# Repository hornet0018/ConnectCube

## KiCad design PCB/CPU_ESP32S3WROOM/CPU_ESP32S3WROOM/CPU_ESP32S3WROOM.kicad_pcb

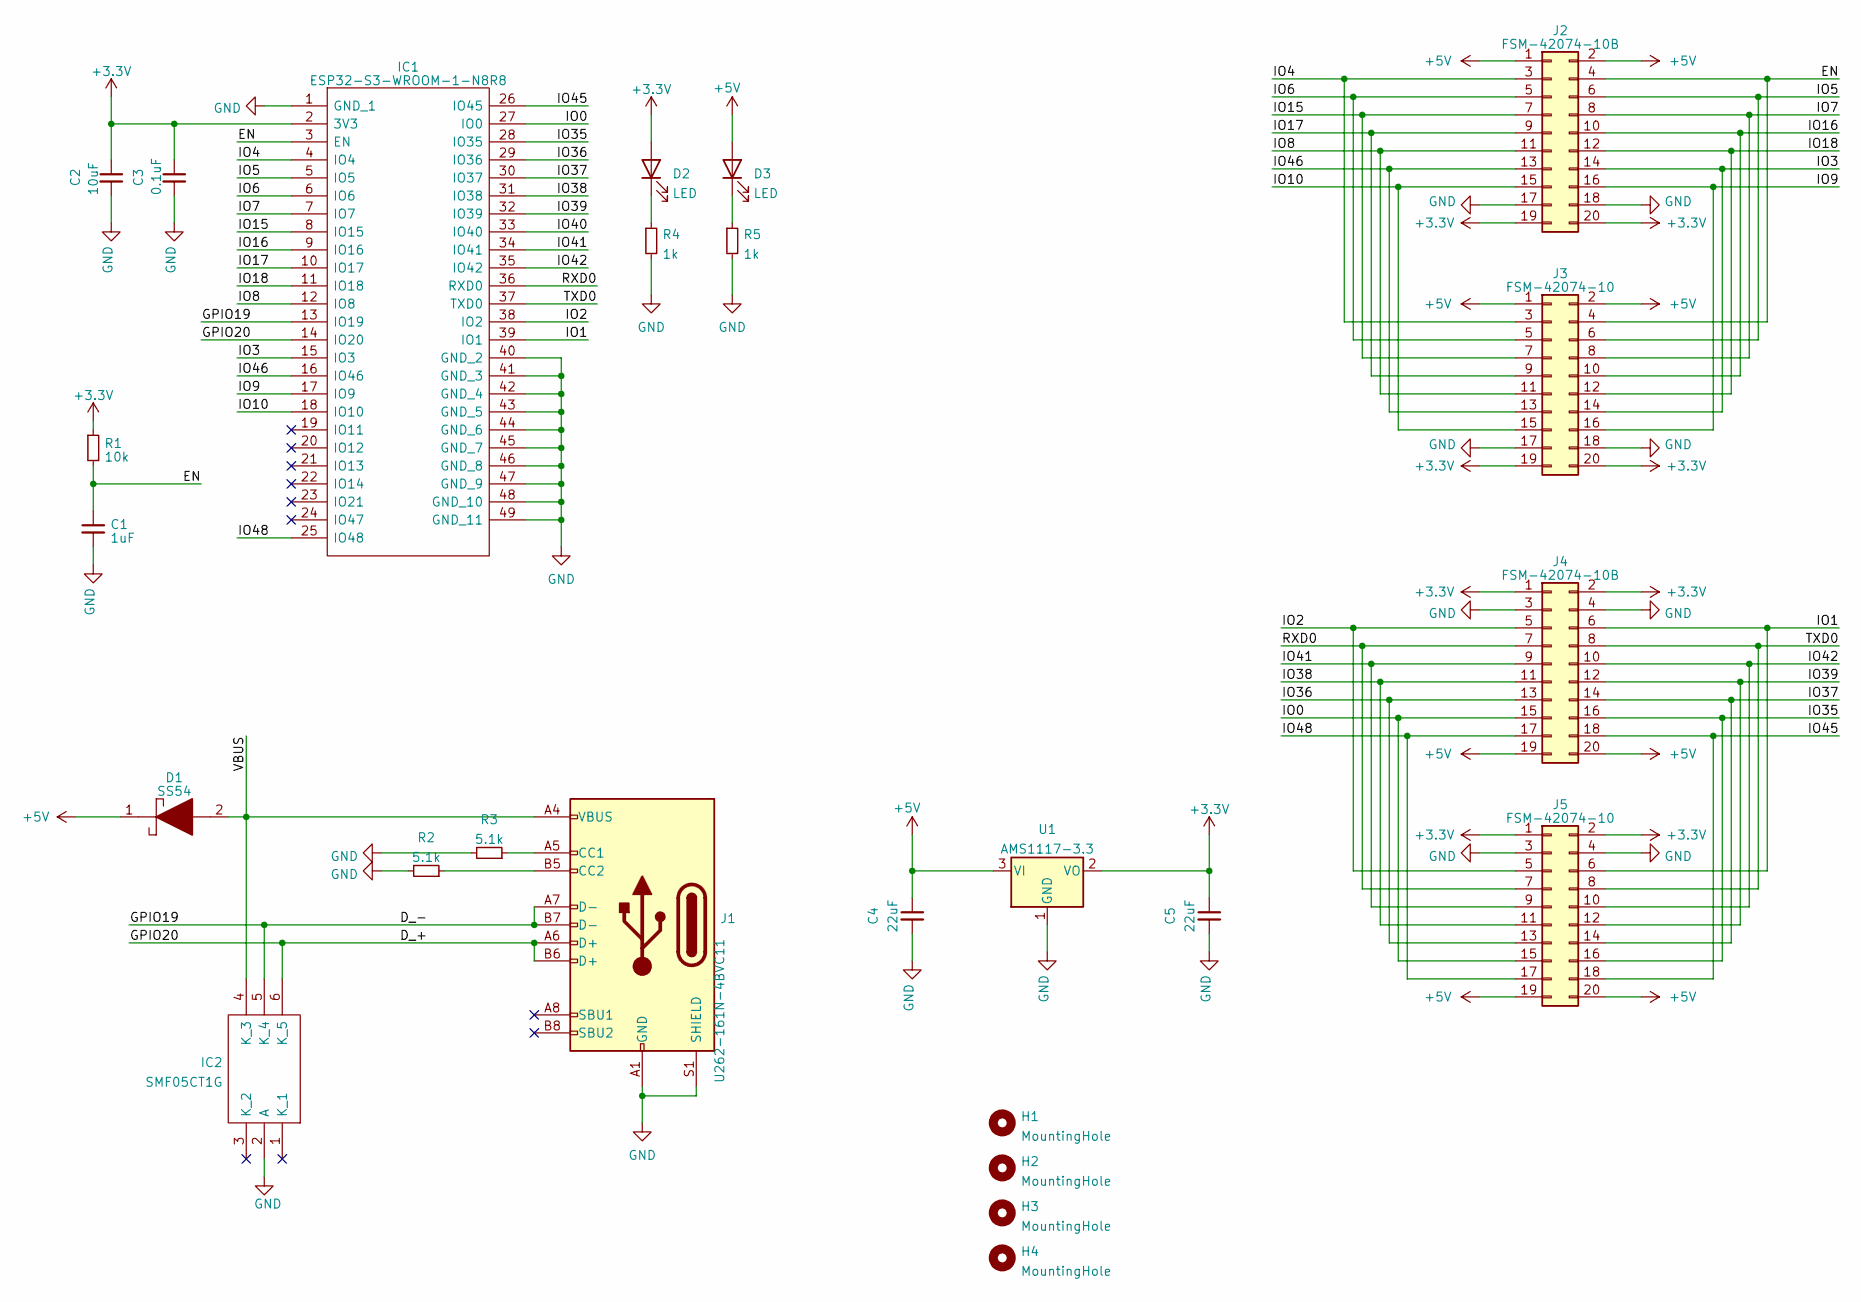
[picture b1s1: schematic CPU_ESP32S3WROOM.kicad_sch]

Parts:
C1: 1uF; C_0603_1608Metric_Pad1.08x0.95mm_HandSolder
C2: 10uF; C_0603_1608Metric_Pad1.08x0.95mm_HandSolder
C3: 0.1uF; C_0603_1608Metric_Pad1.08x0.95mm_HandSolder
C4, C5: 22uF; C_0603_1608Metric_Pad1.08x0.95mm_HandSolder
D1: SS54; DIOM5026X262N; Manufacturer_Part_Number SS54
D2, D3: LED; LED_0603_1608Metric_Pad1.05x0.95mm_HandSolder
H1, H2, H3, H4: MountingHole; MountingHole_3.2mm_M3_Pad_Via
IC1: ESP32-S3-WROOM-1-N8R8; ESP32S3WROOM1N8R8; Manufacturer_Part_Number ESP32-S3-WROOM-1-N8R8; Mouser Part Number 356-EP32S3WROOM1N8R8
IC2: SMF05CT1G; SOT65P210X110-6N; Manufacturer_Part_Number SMF05CT1G; Mouser Part Number 863-SMF05CT1G
J1: U262-161N-4BVC11; U262-16XN-4BVC11
J2, J4: FSM-42074-10B; PinSocket_2x10_P2.54mm_Vertical_SMD
J3, J5: FSM-42074-10; PinHeader_2x10_P2.54mm_Vertical_SMD
R1: 10k; R_0603_1608Metric_Pad0.98x0.95mm_HandSolder
R2, R3: 5.1k; R_0603_1608Metric_Pad0.98x0.95mm_HandSolder
R4, R5: 1k; R_0603_1608Metric_Pad0.98x0.95mm_HandSolder
U1: AMS1117-3.3; SOT-223-3_TabPin2

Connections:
+3V3: C2.1, C3.1, C5.1, D2.2 (A), IC1.2 (3V3), J2.19, J2.20, J3.19, J3.20, J4.1, J4.2, J5.1, J5.2, R1.1, U1.2 (VO)
+5V: C4.1, D1.1, D3.2 (A), J2.1, J2.2, J3.1, J3.2, J4.19, J4.20, J5.19, J5.20, U1.3 (VI)
/D_+: IC1.14 (IO20), IC2.6 (K_5), J1.A6 (D+), J1.B6 (D+)
/D_-: IC1.13 (IO19), IC2.5 (K_4), J1.A7 (D-), J1.B7 (D-)
/EN: C1.1, IC1.3 (EN), J2.4, J3.4, R1.2
/IO0: IC1.27 (IO0), J4.15, J5.15
/IO1: IC1.39 (IO1), J4.6, J5.6
/IO2: IC1.38 (IO2), J4.5, J5.5
/IO3: IC1.15 (IO3), J2.14, J3.14
/IO4: IC1.4 (IO4), J2.3, J3.3
/IO5: IC1.5 (IO5), J2.6, J3.6
/IO6: IC1.6 (IO6), J2.5, J3.5
/IO7: IC1.7 (IO7), J2.8, J3.8
/IO8: IC1.12 (IO8), J2.11, J3.11
/IO9: IC1.17 (IO9), J2.16, J3.16
/IO10: IC1.18 (IO10), J2.15, J3.15
/IO15: IC1.8 (IO15), J2.7, J3.7
/IO16: IC1.9 (IO16), J2.10, J3.10
/IO17: IC1.10 (IO17), J2.9, J3.9
/IO18: IC1.11 (IO18), J2.12, J3.12
/IO35: IC1.28 (IO35), J4.16, J5.16
/IO36: IC1.29 (IO36), J4.13, J5.13
/IO37: IC1.30 (IO37), J4.14, J5.14
/IO38: IC1.31 (IO38), J4.11, J5.11
/IO39: IC1.32 (IO39), J4.12, J5.12
/IO40: IC1.33 (IO40)
/IO41: IC1.34 (IO41), J4.9, J5.9
/IO42: IC1.35 (IO42), J4.10, J5.10
/IO45: IC1.26 (IO45), J4.18, J5.18
/IO46: IC1.16 (IO46), J2.13, J3.13
/IO48: IC1.25 (IO48), J4.17, J5.17
/RXD0: IC1.36 (RXD0), J4.7, J5.7
/TXD0: IC1.37 (TXD0), J4.8, J5.8
/VBUS: D1.2, IC2.4 (K_3), J1.A4 (VBUS), J1.A9 (VBUS), J1.B4 (VBUS), J1.B9 (VBUS)
GND: C1.2, C2.2, C3.2, C4.2, C5.2, IC1.1 (GND_1), IC1.40 (GND_2), IC1.41 (GND_3), IC1.42 (GND_4), IC1.43 (GND_5), IC1.44 (GND_6), IC1.45 (GND_7), IC1.46 (GND_8), IC1.47 (GND_9), IC1.48 (GND_10), IC1.49 (GND_11), IC2.2 (A), J1.A1 (GND), J1.A12 (GND), J1.B1 (GND), J1.B12 (GND), J1.S1 (SHIELD), J2.17, J2.18, J3.17, J3.18, J4.3, J4.4, J5.3, J5.4, R2.2, R3.2, R4.2, R5.2, U1.1 (GND)
unnamed: D2.1 (K), R4.1
unnamed: D3.1 (K), R5.1
unnamed: J1.A5 (CC1), R3.1
unnamed: J1.B5 (CC2), R2.1

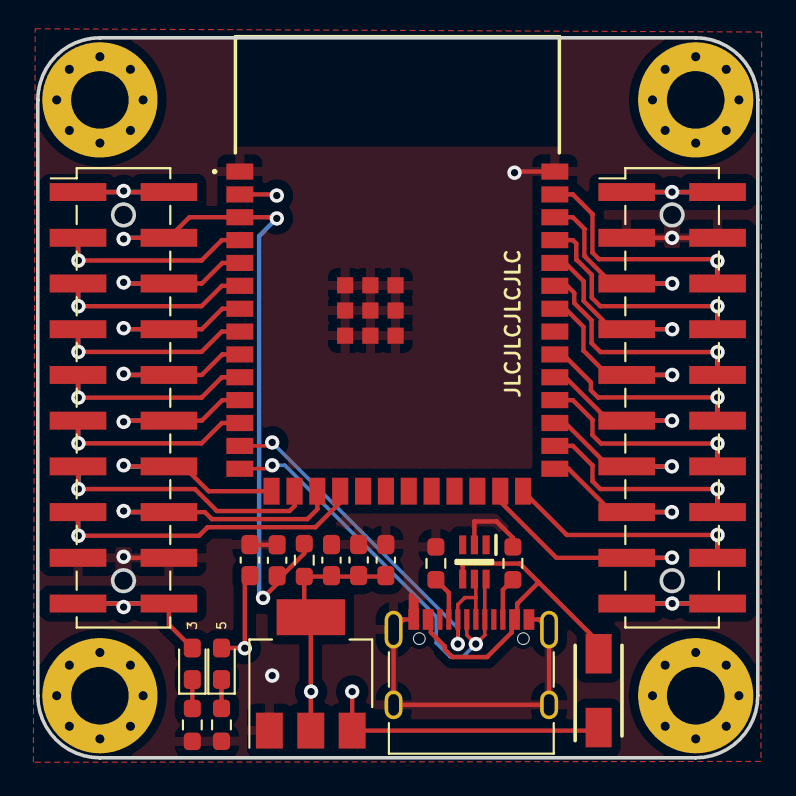
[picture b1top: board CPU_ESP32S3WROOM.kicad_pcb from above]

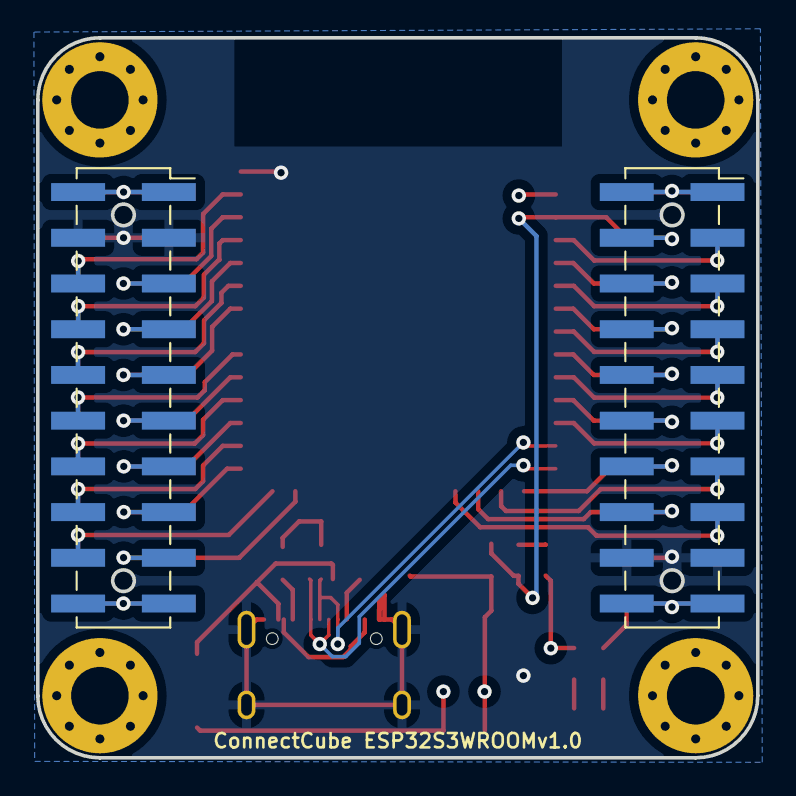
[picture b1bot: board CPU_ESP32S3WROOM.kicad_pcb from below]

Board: 6 copper layers, 40.0 x 40.0 mm, 25 parts (2 on the bottom side), 38 nets.

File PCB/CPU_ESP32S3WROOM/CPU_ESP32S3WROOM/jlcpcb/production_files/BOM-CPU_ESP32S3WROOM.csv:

Comment,Designator,Footprint,LCSC
0.1uF,C3,C_0603_1608Metric_Pad1.08x0.95mm_HandSolder,C14858
1uF,C1,C_0603_1608Metric_Pad1.08x0.95mm_HandSolder,C15849
SMF05CT1G,IC2,SOT65P210X110-6N,C15879
10uF,C2,C_0603_1608Metric_Pad1.08x0.95mm_HandSolder,C19702
1k,"R4,R5",R_0603_1608Metric_Pad0.98x0.95mm_HandSolder,C21190
SS54,D1,DIOM5026X262N,C22452
5.1k,"R2,R3",R_0603_1608Metric_Pad0.98x0.95mm_HandSolder,C23186
10k,R1,R_0603_1608Metric_Pad0.98x0.95mm_HandSolder,C25804
U262-161N-4BVC11,J1,U262-16XN-4BVC11,C319148
22uF,"C4,C5",C_0603_1608Metric_Pad1.08x0.95mm_HandSolder,C59461
AMS1117-3.3,U1,SOT-223-3_TabPin2,C6186
LED,D3,LED_0603_1608Metric_Pad1.05x0.95mm_HandSolder,C72041
LED,D2,LED_0603_1608Metric_Pad1.05x0.95mm_HandSolder,C72043
FSM-42074-10,J5,PinHeader_2x10_P2.54mm_Vertical_SMD,
MountingHole,H2,MountingHole_3.2mm_M3_Pad_Via,
MountingHole,H4,MountingHole_3.2mm_M3_Pad_Via,
MountingHole,H3,MountingHole_3.2mm_M3_Pad_Via,
MountingHole,H1,MountingHole_3.2mm_M3_Pad_Via,
FSM-42074-10,J3,PinHeader_2x10_P2.54mm_Vertical_SMD,
ESP32-S3-WROOM-1-N8R8,IC1,ESP32S3WROOM1N8R8,
FSM-42074-10B,J4,PinSocket_2x10_P2.54mm_Vertical_SMD,
FSM-42074-10B,J2,PinSocket_2x10_P2.54mm_Vertical_SMD,

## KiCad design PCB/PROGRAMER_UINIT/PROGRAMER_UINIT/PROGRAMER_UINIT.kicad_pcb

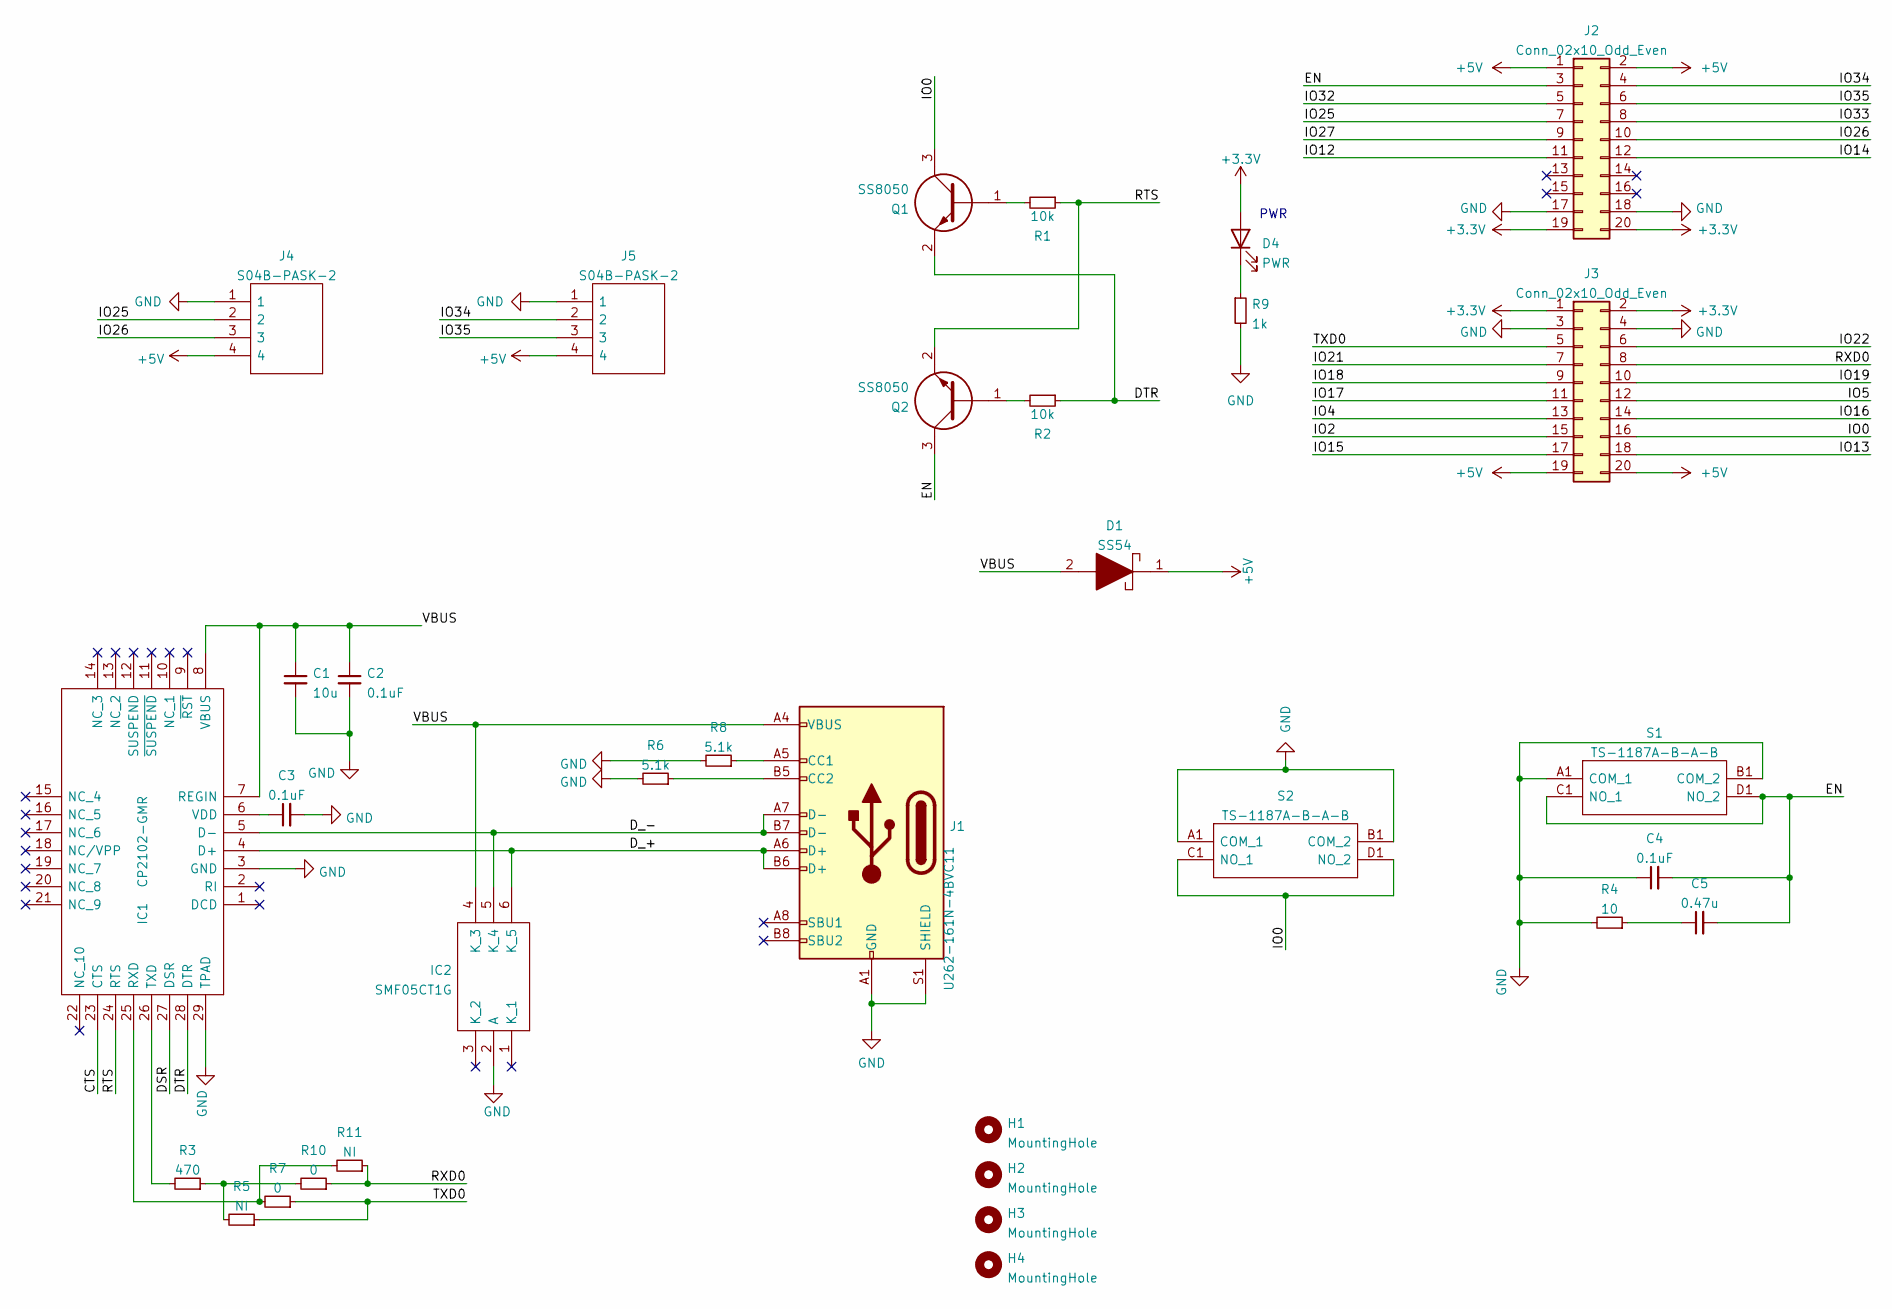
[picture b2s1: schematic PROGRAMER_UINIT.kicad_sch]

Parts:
C1: 10u; C_0603_1608Metric_Pad1.08x0.95mm_HandSolder
C2, C3, C4: 0.1uF; C_0603_1608Metric_Pad1.08x0.95mm_HandSolder
C5: 0.47u; C_0603_1608Metric_Pad1.08x0.95mm_HandSolder
D1: SS54; DIOM5026X262N; Manufacturer_Part_Number SS54
D4: PWR; LED_0603_1608Metric_Pad1.05x0.95mm_HandSolder
H1, H2, H3, H4: MountingHole; MountingHole_3.2mm_M3_Pad_Via
IC1: CP2102-GMR; QFN50P500X500X100-29N-D; Manufacturer_Part_Number CP2102-GMR; Mouser Part Number 634-CP2102-GMR
IC2: SMF05CT1G; SOT65P210X110-6N; Manufacturer_Part_Number SMF05CT1G; Mouser Part Number 863-SMF05CT1G
J1: U262-161N-4BVC11; U262-16XN-4BVC11
J2, J3: Conn_02x10_Odd_Even; PinHeader_2x10_P2.54mm_Vertical
J4, J5: S04B-PASK-2; S04BPASK2; Manufacturer_Part_Number S04B-PASK-2
Q1, Q2: SS8050; SOT-23; Manufacturer_Part_Number MMSS8050-H-TP; Mouser Part Number 833-MMSS8050-H-TP
R1, R2: 10k; R_0603_1608Metric_Pad0.98x0.95mm_HandSolder
R3: 470; R_0603_1608Metric_Pad0.98x0.95mm_HandSolder
R4: 10; R_0603_1608Metric_Pad0.98x0.95mm_HandSolder
R5, R11: NI; R_0603_1608Metric_Pad0.98x0.95mm_HandSolder
R6, R8: 5.1k; R_0603_1608Metric_Pad0.98x0.95mm_HandSolder
R7, R10: 0; R_0603_1608Metric_Pad0.98x0.95mm_HandSolder
R9: 1k; R_0603_1608Metric_Pad0.98x0.95mm_HandSolder
S1, S2: TS-1187A-B-A-B; TS1187ABAB; Manufacturer_Part_Number TS-1187A-B-A-B

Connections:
+3V3: D4.2 (A), J2.19, J2.20, J3.1, J3.2
+5V: D1.1, J2.1, J2.2, J3.19, J3.20, J4.4, J5.4
/CTS: IC1.23 (CTS)
/DSR: IC1.27 (DSR)
/DTR: IC1.28 (DTR), Q1.2, R2.1
/D_+: IC1.4 (D+), IC2.6 (K_5), J1.A6 (D+), J1.B6 (D+)
/D_-: IC1.5 (D-), IC2.5 (K_4), J1.A7 (D-), J1.B7 (D-)
/EN: C4.2, C5.2, J2.3, Q2.3, S1.C1 (NO_1), S1.D1 (NO_2)
/IO0: J3.16, Q1.3, S2.C1 (NO_1), S2.D1 (NO_2)
/IO2: J3.15
/IO4: J3.13
/IO5: J3.12
/IO12: J2.11
/IO13: J3.18
/IO14: J2.12
/IO15: J3.17
/IO16: J3.14
/IO17: J3.11
/IO18: J3.9
/IO19: J3.10
/IO21: J3.7
/IO22: J3.6
/IO25: J2.7, J4.2
/IO26: J2.10, J4.3
/IO27: J2.9
/IO32: J2.5
/IO33: J2.8
/IO34: J2.4, J5.2
/IO35: J2.6, J5.3
/RTS: IC1.24 (RTS), Q2.2, R1.1
/RXD0: J3.8, R10.1, R11.1; also elsewhere on the board
/TXD0: J3.5, R5.1, R7.1
/VBUS: C1.1, C2.1, D1.2, IC1.7 (REGIN), IC1.8 (VBUS), IC2.4 (K_3), J1.A4 (VBUS), J1.A9 (VBUS), J1.B4 (VBUS), J1.B9 (VBUS)
GND: C1.2, C2.2, C3.2, C4.1, IC1.3 (GND), IC1.29 (TPAD), IC2.2 (A), J1.A1 (GND), J1.A12 (GND), J1.B1 (GND), J1.B12 (GND), J1.S1 (SHIELD), J2.17, J2.18, J3.3, J3.4, J4.1, J5.1, R4.2, R6.2, R8.2, R9.2, S1.A1 (COM_1), S1.B1 (COM_2), S2.A1 (COM_1), S2.B1 (COM_2)
unnamed: C3.1, IC1.6 (VDD)
unnamed: C5.1, R4.1
unnamed: D4.1 (K), R9.1
unnamed: IC1.25 (RXD), R7.2, R11.2
unnamed: IC1.26 (TXD), R3.2
unnamed: J1.A5 (CC1), R8.1
unnamed: J1.B5 (CC2), R6.1
unnamed: Q1.1, R1.2
unnamed: Q2.1, R2.2
unnamed 43: R3.1, R5.2, R10.2; also elsewhere on the board

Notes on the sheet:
PWR

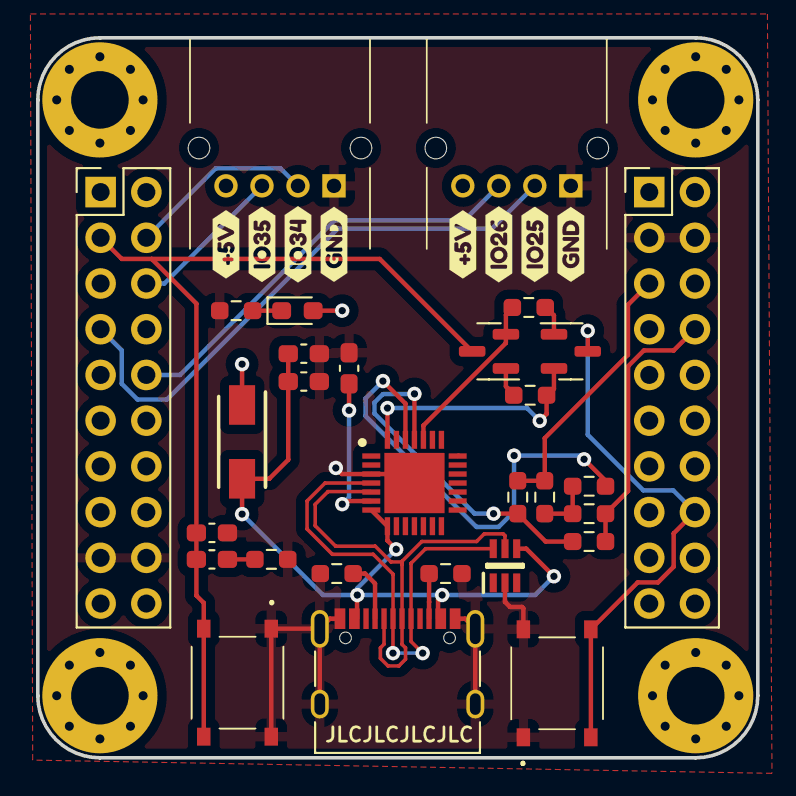
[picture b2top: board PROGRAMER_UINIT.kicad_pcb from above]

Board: 6 copper layers, 40.0 x 40.0 mm, 42 parts (1 on the bottom side), 26 nets.

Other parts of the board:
Rd: 0; R_0603_1608Metric_Pad0.98x0.95mm_HandSolder
kibuzzard-642EE370: G***; kibuzzard-642EE370
kibuzzard-642F6DD4, kibuzzard-642F6DD4#2: G***; kibuzzard-642F6DD4
kibuzzard-642F6DE4: G***; kibuzzard-642F6DE4
kibuzzard-642F6DEF: G***; kibuzzard-642F6DEF
kibuzzard-642F6DF7, kibuzzard-642F6DF7#2: G***; kibuzzard-642F6DF7
kibuzzard-642F6E1E: G***; kibuzzard-642F6E1E
kibuzzard-642F6E25: G***; kibuzzard-642F6E25

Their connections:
/RXD0: Rd.1; also elsewhere on the board
unnamed 43: Rd.2; also elsewhere on the board

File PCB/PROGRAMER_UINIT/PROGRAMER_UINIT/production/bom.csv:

Designator,Footprint,Quantity,Value,LCSC Part #
C1,C_0603_1608Metric_Pad1.08x0.95mm_HandSolder,1,10u,C19702
"C2, C3, C4",C_0603_1608Metric_Pad1.08x0.95mm_HandSolder,3,0.1uF,C14858
C5,C_0603_1608Metric_Pad1.08x0.95mm_HandSolder,1,0.47u,C1623
D1,DIOM5026X262N,1,SS54,C22452
D4,LED_0603_1608Metric_Pad1.05x0.95mm_HandSolder,1,PWR,C2286
"H1, H2, H3, H4",MountingHole_3.2mm_M3_Pad_Via,4,MountingHole,
IC1,QFN50P500X500X100-29N-D,1,CP2102-GMR,C6568
IC2,SOT65P210X110-6N,1,SMF05CT1G,C15879
J1,U262-16XN-4BVC11,1,U262-161N-4BVC11,C319148
"J2, J3",PinHeader_2x10_P2.54mm_Vertical,2,Conn_02x10_Odd_Even,
"J4, J5",S04BPASK2,2,S04B-PASK-2,
"Q1, Q2",SOT-23,2,SS8050,C2150
"R1, R2",R_0603_1608Metric_Pad0.98x0.95mm_HandSolder,2,10k,C25804
"R10, R7",R_0603_1608Metric_Pad0.98x0.95mm_HandSolder,2,0,C21189
"R11, R5",R_0603_1608Metric_Pad0.98x0.95mm_HandSolder,2,NI,
R3,R_0603_1608Metric_Pad0.98x0.95mm_HandSolder,1,470,C23179
R4,R_0603_1608Metric_Pad0.98x0.95mm_HandSolder,1,10,C22859
"R6, R8",R_0603_1608Metric_Pad0.98x0.95mm_HandSolder,2,5.1k,C23186
R9,R_0603_1608Metric_Pad0.98x0.95mm_HandSolder,1,1k,C21190
"S1, S2",TS1187ABAB,2,TS-1187A-B-A-B,C318884

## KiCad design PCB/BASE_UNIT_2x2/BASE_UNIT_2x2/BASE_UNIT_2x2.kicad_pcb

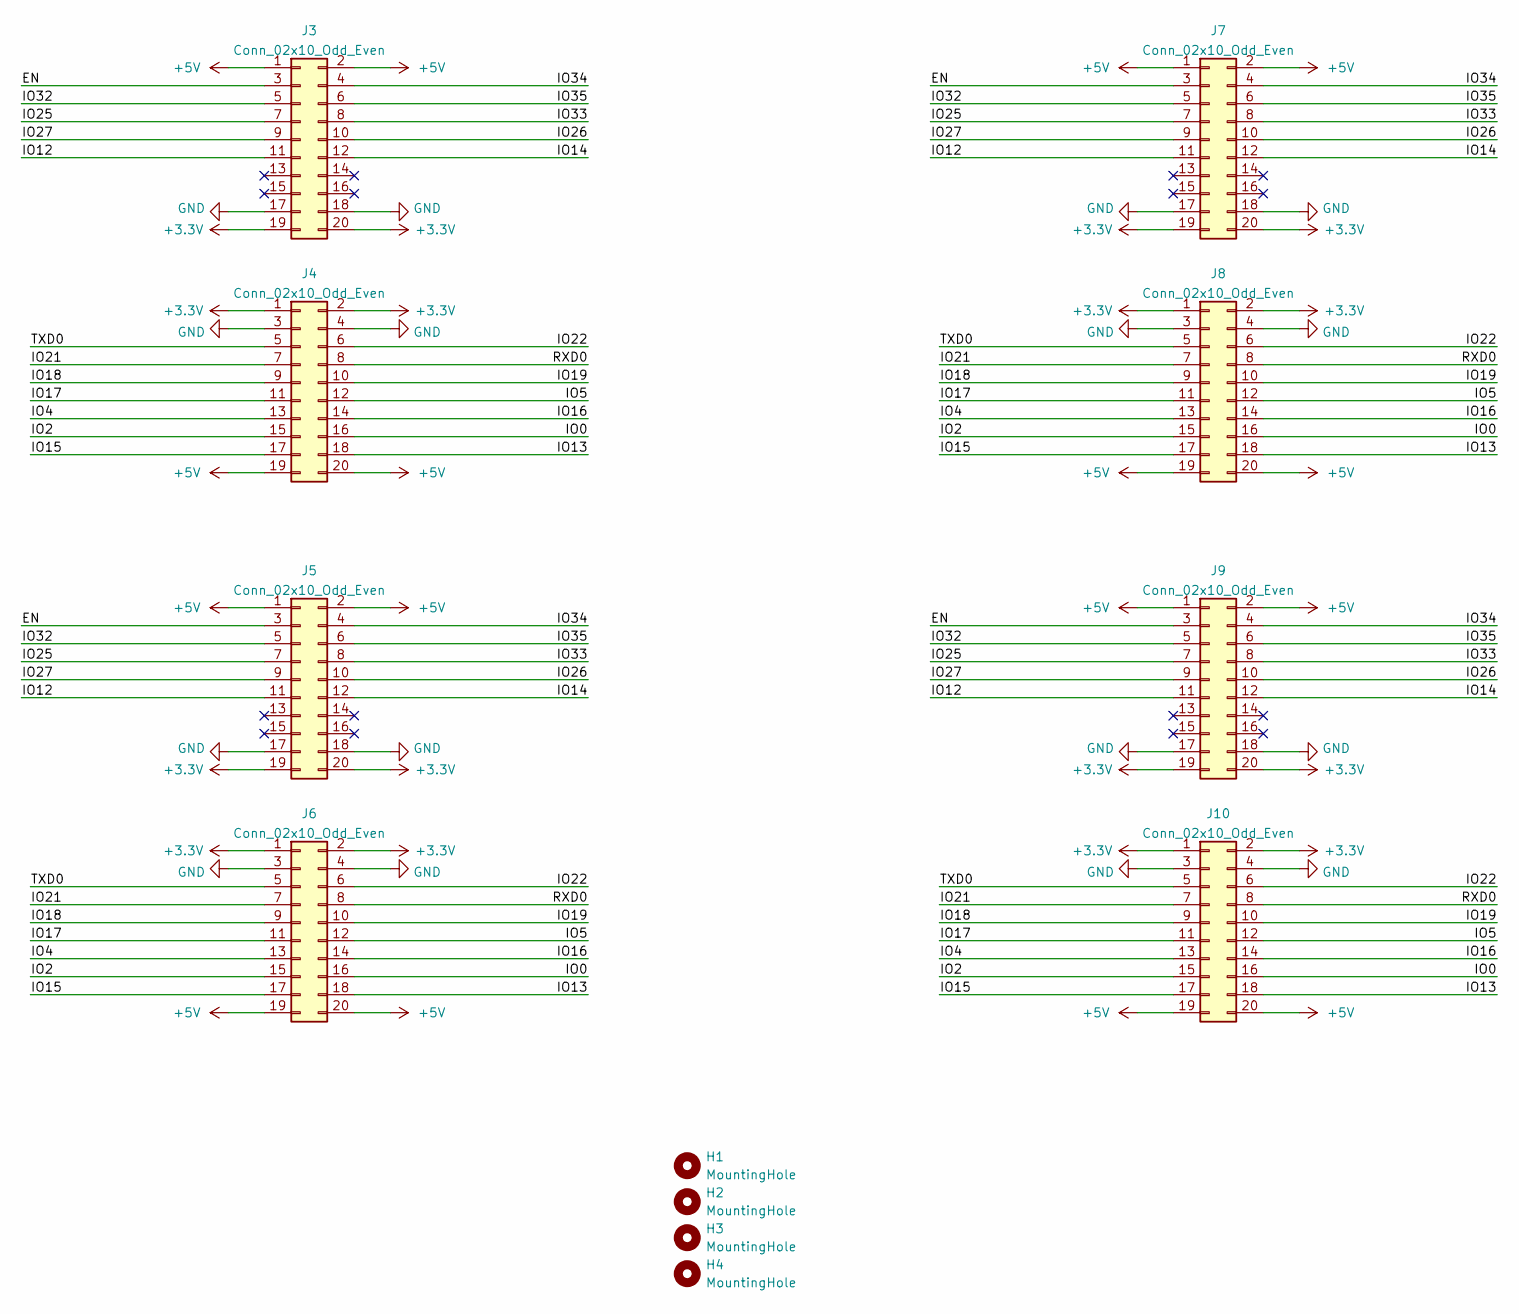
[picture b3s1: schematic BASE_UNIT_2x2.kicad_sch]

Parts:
H1, H2, H3, H4: MountingHole; MountingHole_3.2mm_M3_Pad_Via
J3, J4, J5, J6, J7, J8, J9, J10: Conn_02x10_Odd_Even; PinHeader_2x10_P2.54mm_Vertical

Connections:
+3V3: J3.19, J3.20, J4.1, J4.2, J5.19, J5.20, J6.1, J6.2, J7.19, J7.20, J8.1, J8.2, J9.19, J9.20, J10.1, J10.2
+5V: J3.1, J3.2, J4.19, J4.20, J5.1, J5.2, J6.19, J6.20, J7.1, J7.2, J8.19, J8.20, J9.1, J9.2, J10.19, J10.20
/EN: J3.3, J5.3, J7.3, J9.3
/IO0: J4.16, J6.16, J8.16, J10.16
/IO2: J4.15, J6.15, J8.15, J10.15
/IO4: J4.13, J6.13, J8.13, J10.13
/IO5: J4.12, J6.12, J8.12, J10.12
/IO12: J3.11, J5.11, J7.11, J9.11
/IO13: J4.18, J6.18, J8.18, J10.18
/IO14: J3.12, J5.12, J7.12, J9.12
/IO15: J4.17, J6.17, J8.17, J10.17
/IO16: J4.14, J6.14, J8.14, J10.14
/IO17: J4.11, J6.11, J8.11, J10.11
/IO18: J4.9, J6.9, J8.9, J10.9
/IO19: J4.10, J6.10, J8.10, J10.10
/IO21: J4.7, J6.7, J8.7, J10.7
/IO22: J4.6, J6.6, J8.6, J10.6
/IO25: J3.7, J5.7, J7.7, J9.7
/IO26: J3.10, J5.10, J7.10, J9.10
/IO27: J3.9, J5.9, J7.9, J9.9
/IO32: J3.5, J5.5, J7.5, J9.5
/IO33: J3.8, J5.8, J7.8, J9.8
/IO34: J3.4, J5.4, J7.4, J9.4
/IO35: J3.6, J5.6, J7.6, J9.6
/RXD0: J4.8, J6.8, J8.8, J10.8
/TXD0: J4.5, J6.5, J8.5, J10.5
GND: J3.17, J3.18, J4.3, J4.4, J5.17, J5.18, J6.3, J6.4, J7.17, J7.18, J8.3, J8.4, J9.17, J9.18, J10.3, J10.4

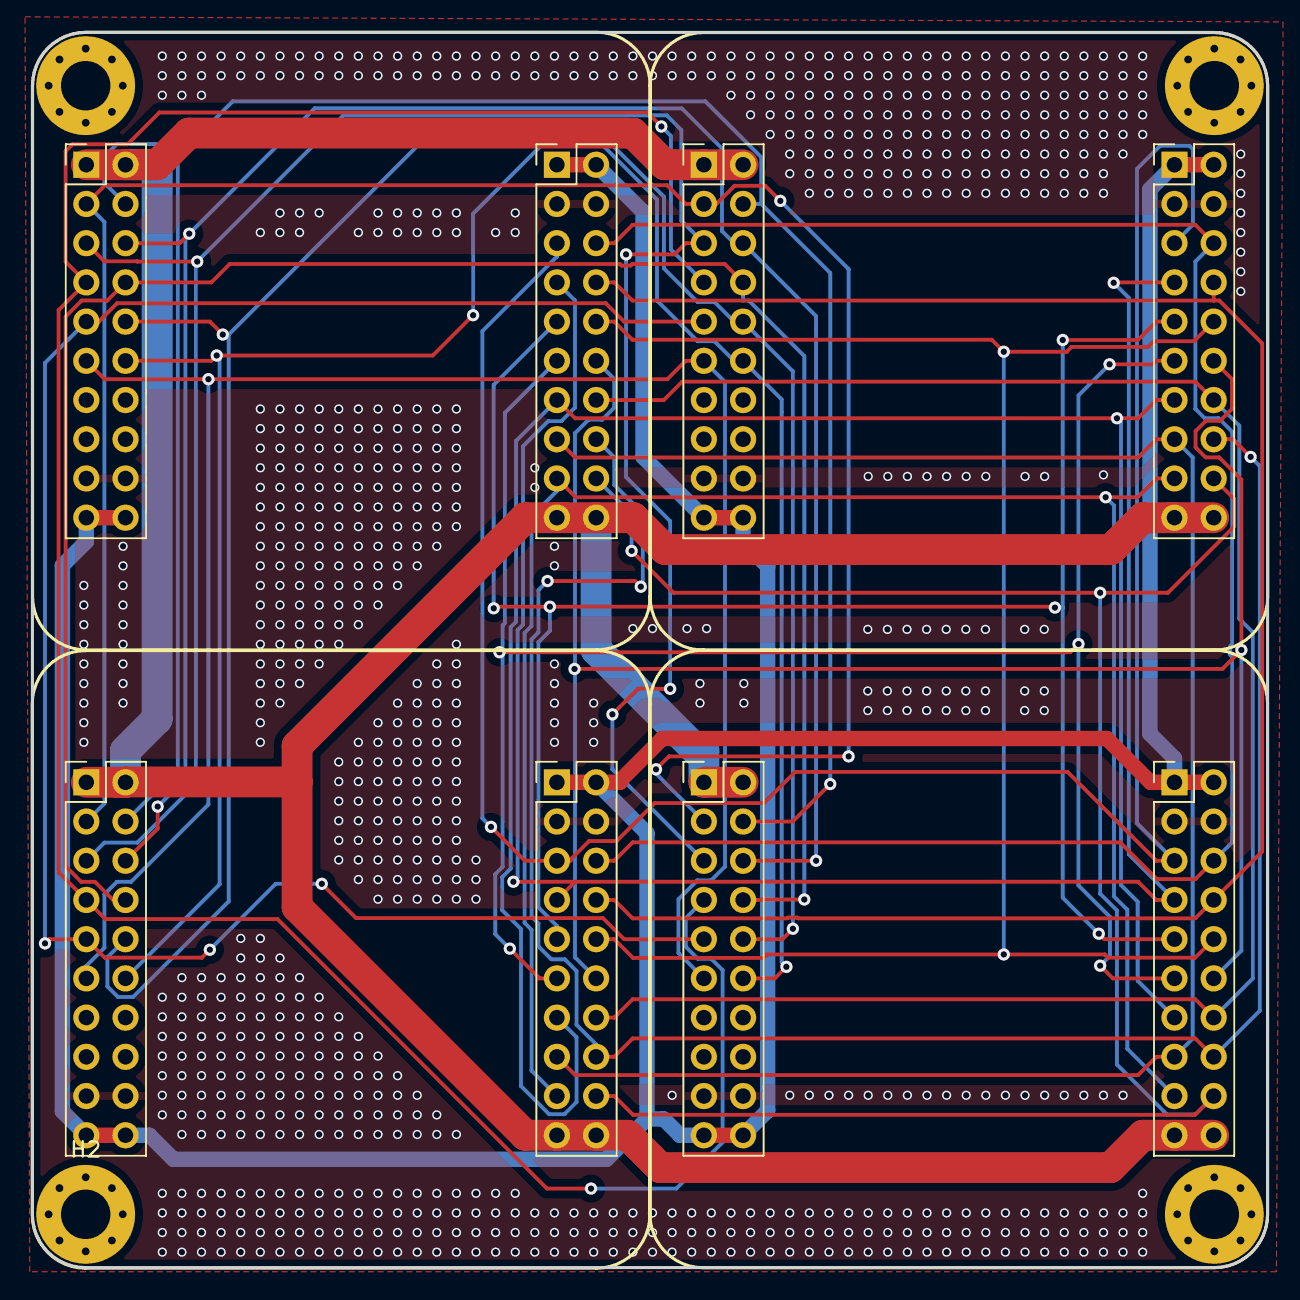
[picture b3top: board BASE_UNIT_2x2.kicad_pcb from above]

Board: 2 copper layers, 80.0 x 80.0 mm, 13 parts (1 on the bottom side), 27 nets.

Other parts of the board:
kibuzzard-642D6EAA: G***; kibuzzard-642D6EAA

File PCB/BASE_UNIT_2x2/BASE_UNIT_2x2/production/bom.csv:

Designator,Footprint,Quantity,Value,LCSC Part #
"H1, H2, H3, H4",MountingHole_3.2mm_M3_Pad_Via,4,MountingHole,
"J10, J3, J4, J5, J6, J7, J8, J9",PinHeader_2x10_P2.54mm_Vertical,8,Conn_02x10_Odd_Even,

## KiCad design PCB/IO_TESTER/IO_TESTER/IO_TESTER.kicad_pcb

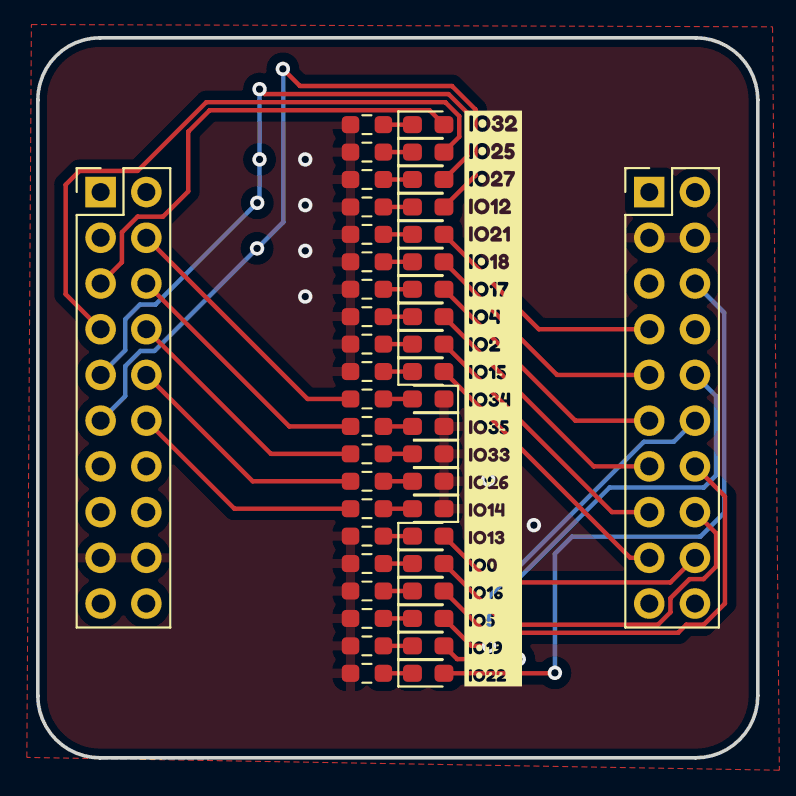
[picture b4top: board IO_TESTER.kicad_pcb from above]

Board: 6 copper layers, 40.0 x 40.0 mm, 46 parts (1 on the bottom side), 45 nets.

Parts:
D1, D2, D3, D4, D5, D6, D7, D8, D9, D10, D11, D12, D13, D14, D15, D16, D17, D18, D19, D20, D21: LED; LED_0603_1608Metric_Pad1.05x0.95mm_HandSolder
J1, J2: Conn_02x10_Odd_Even; PinHeader_2x10_P2.54mm_Vertical
R1, R2, R3, R4, R5, R6, R7, R8, R9, R10, R11, R12, R13, R14, R15, R16, R17, R18, R19, R20, R21: 1k; R_0603_1608Metric_Pad0.98x0.95mm_HandSolder
kibuzzard-6415B1F6: G***; kibuzzard-6415B1F6
kibuzzard-6415BE7B: G***; kibuzzard-6415BE7B

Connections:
+3V3: J1.19, J1.20, J2.1, J2.2
+5V: J1.1, J1.2, J2.19, J2.20
/IO0: D17.2 (A), J2.16
/IO2: D9.2 (A), J2.15
/IO4: D8.2 (A), J2.13
/IO5: D19.2 (A), J2.12
/IO12: D4.2 (A), J1.11
/IO13: D16.2 (A), J2.18
/IO14: J1.12, R11.2
/IO15: D10.2 (A), J2.17
/IO16: D18.2 (A), J2.14
/IO17: D7.2 (A), J2.11
/IO18: D6.2 (A), J2.9
/IO19: D20.2 (A), J2.10
/IO21: D5.2 (A), J2.7
/IO22: D21.2 (A), J2.6
/IO25: D2.2 (A), J1.7
/IO26: J1.10, R12.2
/IO27: D3.2 (A), J1.9
/IO32: D1.2 (A), J1.5
/IO33: J1.8, R13.2
/IO34: J1.4, R15.2
/IO35: J1.6, R14.2
GND: D11.1 (K), D12.1 (K), D13.1 (K), D14.1 (K), D15.1 (K), J1.17, J1.18, J2.3, J2.4, R1.1, R2.1, R3.1, R4.1, R5.1, R6.1, R7.1, R8.1, R9.1, R10.1, R16.1, R17.1, R18.1, R19.1, R20.1, R21.1
unnamed: D1.1 (K), R1.2
unnamed: D2.1 (K), R2.2
unnamed: D3.1 (K), R3.2
unnamed: D4.1 (K), R4.2
unnamed: D5.1 (K), R5.2
unnamed: D6.1 (K), R6.2
unnamed: D7.1 (K), R7.2
unnamed: D8.1 (K), R8.2
unnamed: D9.1 (K), R9.2
unnamed: D10.1 (K), R10.2
unnamed: D11.2 (A), R11.1
unnamed: D12.2 (A), R12.1
unnamed: D13.2 (A), R13.1
unnamed: D14.2 (A), R14.1
unnamed: D15.2 (A), R15.1
unnamed: D16.1 (K), R16.2
unnamed: D17.1 (K), R17.2
unnamed: D18.1 (K), R18.2
unnamed: D19.1 (K), R19.2
unnamed: D20.1 (K), R20.2
unnamed: D21.1 (K), R21.2

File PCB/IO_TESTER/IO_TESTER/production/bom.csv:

Designator,Footprint,Quantity,Value,LCSC Part #
"D1, D10, D11, D12, D13, D14, D15, D16, D17, D18, D19, D2, D20, D21, D3, D4, D5, D6, D7, D8, D9",LED_0603_1608Metric_Pad1.05x0.95mm_HandSolder,21,LED,C72041
"H1, H2, H3, H4",MountingHole_3.2mm_M3_Pad_Via,4,MountingHole,
"J1, J2",PinHeader_2x10_P2.54mm_Vertical,2,Conn_02x10_Odd_Even,
"R1, R10, R11, R12, R13, R14, R15, R16, R17, R18, R19, R2, R20, R21, R3, R4, R5, R6, R7, R8, R9",R_0603_1608Metric_Pad0.98x0.95mm_HandSolder,21,1k,C21190

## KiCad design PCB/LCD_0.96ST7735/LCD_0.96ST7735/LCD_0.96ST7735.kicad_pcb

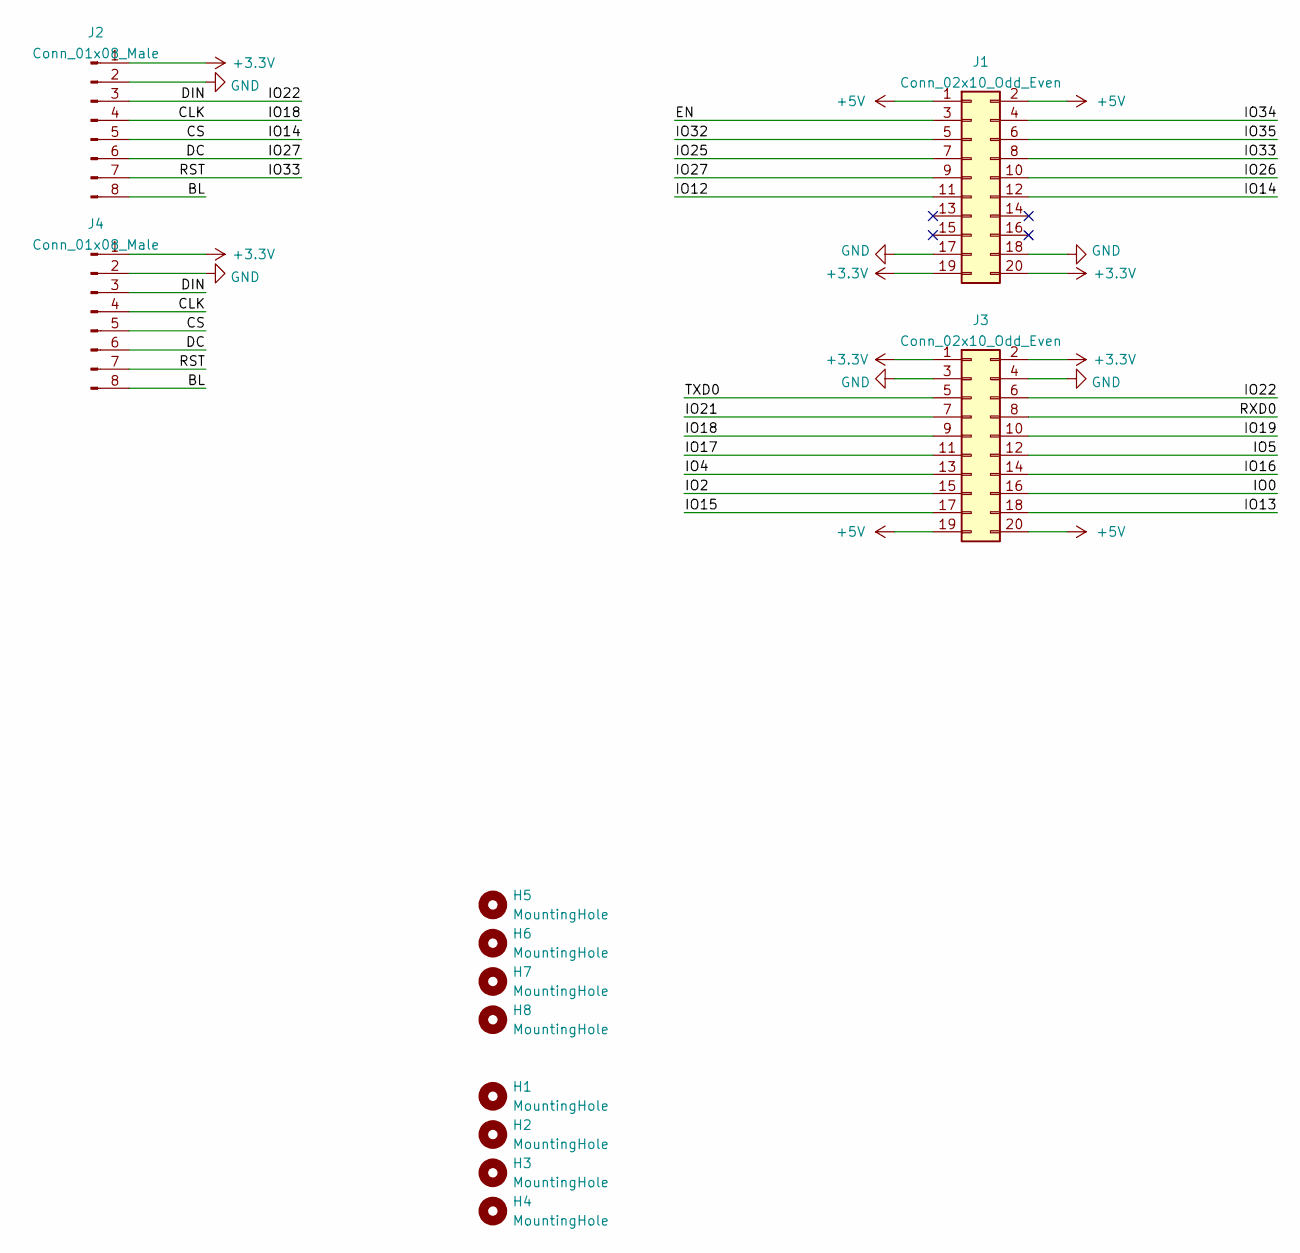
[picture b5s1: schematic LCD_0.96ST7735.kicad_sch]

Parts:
H1, H2, H3, H4: MountingHole; MountingHole_3.2mm_M3_Pad_Via
H5, H6, H7, H8: MountingHole; MountingHole_3.2mm_M3
J1, J3: Conn_02x10_Odd_Even; PinHeader_2x10_P2.54mm_Vertical
J2, J4: Conn_01x08_Male; PinHeader_1x08_P2.00mm_Vertical

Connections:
+3V3: J1.19, J1.20, J2.1, J3.1, J3.2, J4.1
+5V: J1.1, J1.2, J3.19, J3.20
/BL: J2.8, J4.8
/CLK: J2.4, J3.9, J4.4
/CS: J1.12, J2.5, J4.5
/DC: J1.9, J2.6, J4.6
/DIN: J2.3, J3.6, J4.3
/EN: J1.3
/IO0: J3.16
/IO2: J3.15
/IO4: J3.13
/IO5: J3.12
/IO12: J1.11
/IO13: J3.18
/IO15: J3.17
/IO16: J3.14
/IO17: J3.11
/IO19: J3.10
/IO21: J3.7
/IO25: J1.7
/IO26: J1.10
/IO32: J1.5
/IO33: J1.8, J2.7, J4.7
/IO34: J1.4
/IO35: J1.6
/RXD0: J3.8
/TXD0: J3.5
GND: J1.17, J1.18, J2.2, J3.3, J3.4, J4.2

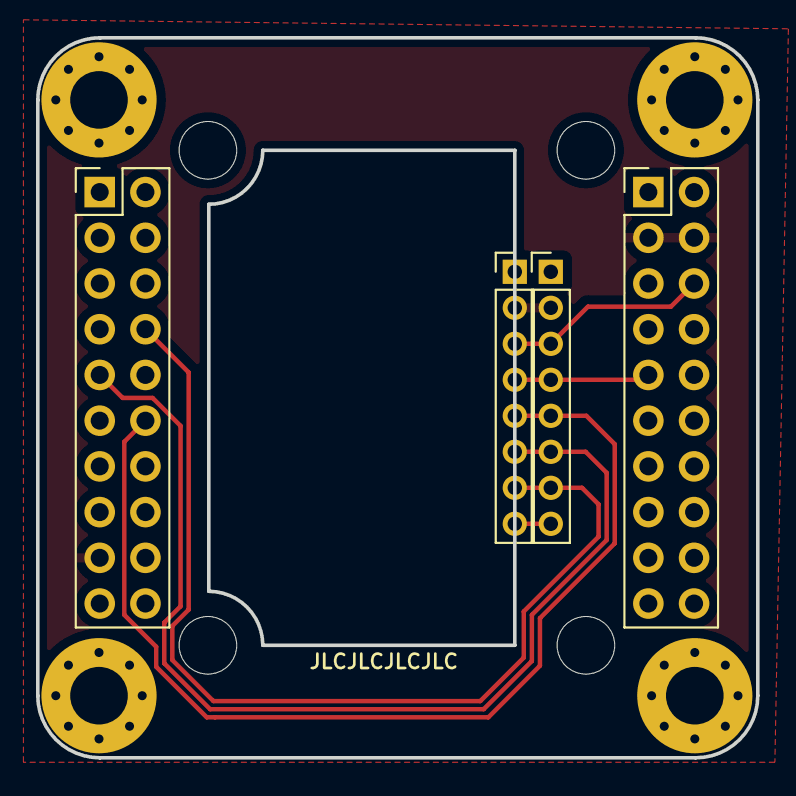
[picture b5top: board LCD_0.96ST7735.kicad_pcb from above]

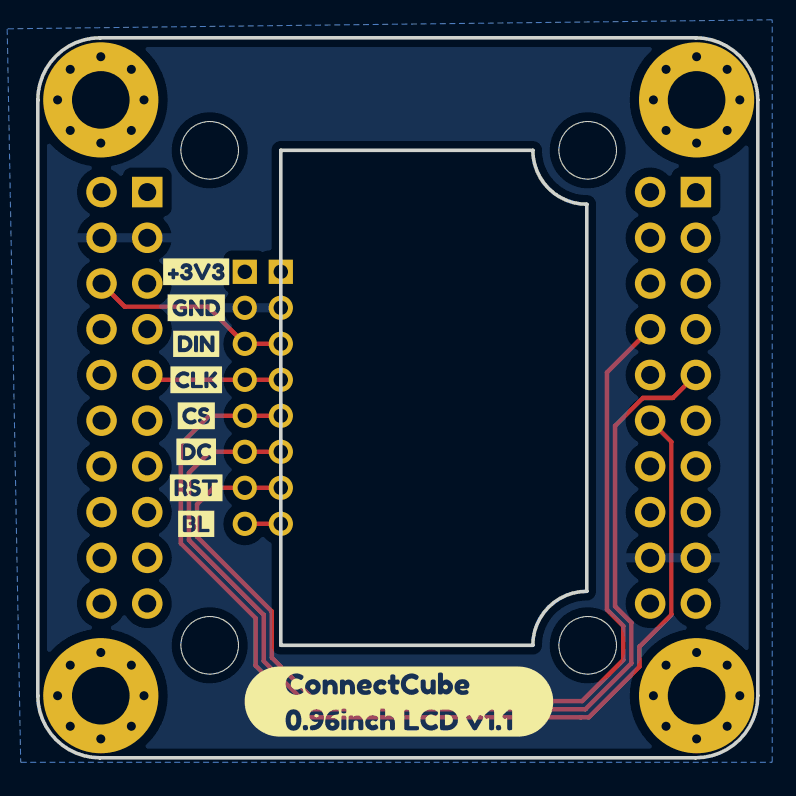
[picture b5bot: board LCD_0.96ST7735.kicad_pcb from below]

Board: 6 copper layers, 40.0 x 40.0 mm, 21 parts (9 on the bottom side), 9 nets.

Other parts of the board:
kibuzzard-640490BE: G***; kibuzzard-640490BE
kibuzzard-640491A0: G***; kibuzzard-640491A0
kibuzzard-6404916C: G***; kibuzzard-6404916C
kibuzzard-6404917C: G***; kibuzzard-6404917C
kibuzzard-64049156: G***; kibuzzard-64049156
kibuzzard-64049163: G***; kibuzzard-64049163
kibuzzard-64049174: G***; kibuzzard-64049174
kibuzzard-64049199: G***; kibuzzard-64049199
kibuzzard-64147912: G***; kibuzzard-64147912

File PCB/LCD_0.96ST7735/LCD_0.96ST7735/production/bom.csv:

Designator,Footprint,Quantity,Value,LCSC Part #
"H1, H2, H3, H4",MountingHole_3.2mm_M3_Pad_Via,4,MountingHole,
"H5, H6, H7, H8",MountingHole_3.2mm_M3,4,MountingHole,
"J1, J3",PinHeader_2x10_P2.54mm_Vertical,2,Conn_02x10_Odd_Even,
"J2, J4",PinHeader_1x08_P2.00mm_Vertical,2,Conn_01x08_Male,
